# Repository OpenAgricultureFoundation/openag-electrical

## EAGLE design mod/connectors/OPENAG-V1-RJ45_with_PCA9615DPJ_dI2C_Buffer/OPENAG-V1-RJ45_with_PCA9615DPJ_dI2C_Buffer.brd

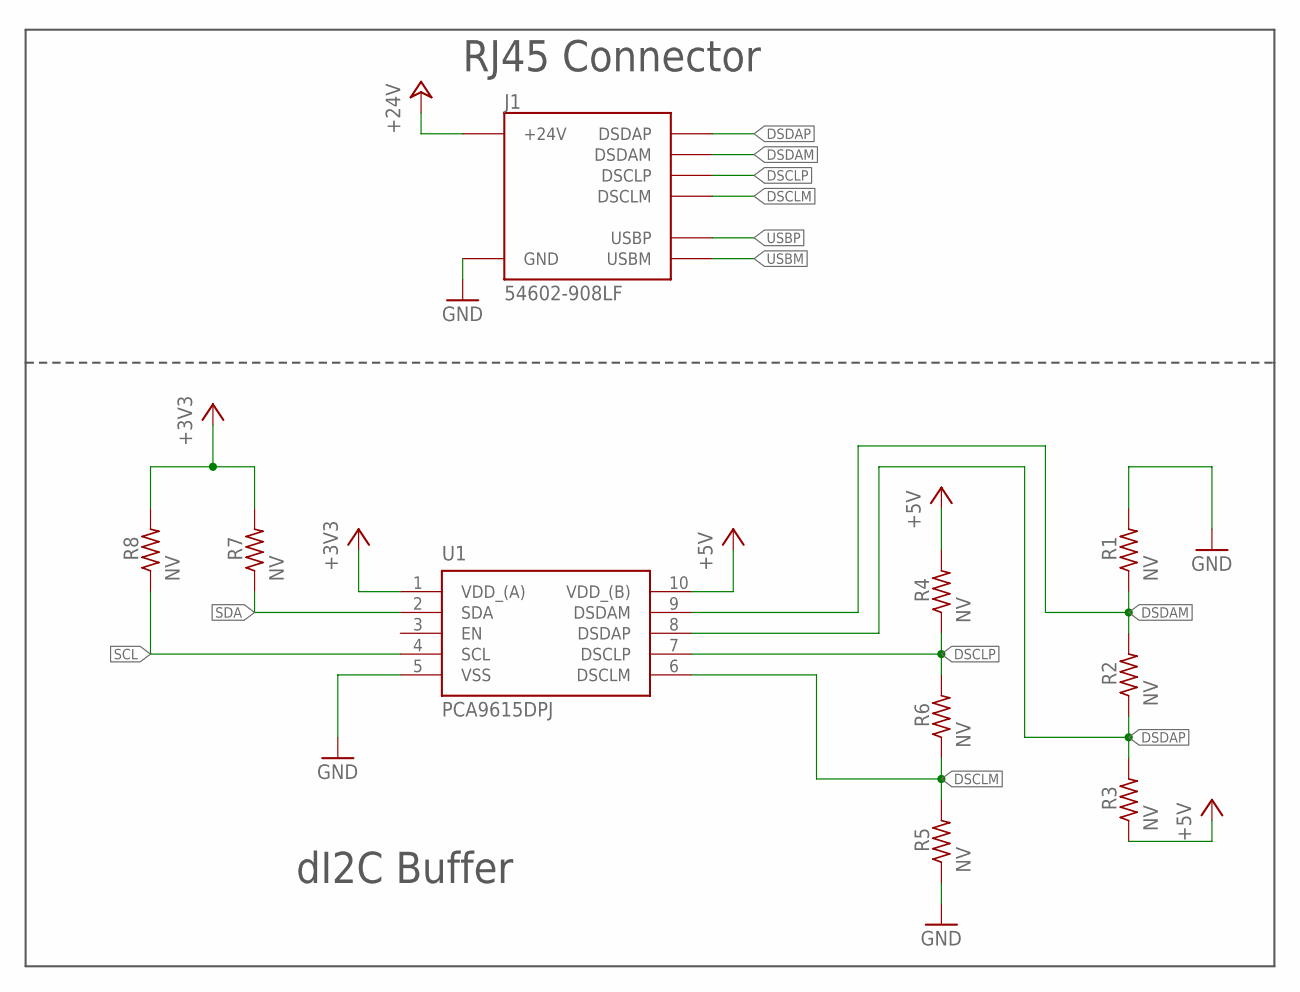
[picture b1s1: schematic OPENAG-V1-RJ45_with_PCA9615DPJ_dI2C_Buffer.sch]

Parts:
J1: 54602-908LF; OPENAG-V1-RJ45
R1, R2, R3, R4, R5, R6, R7, R8: NV; RC0603N
U1: PCA9615DPJ; SOP50P490X110-10N

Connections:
+3V3: R7.2, R8.2, U1.1 (VDD_(A))
+5V: R3.1, R4.2, U1.10 (VDD_(B))
+24V: J1.24V(6) (+24V)
DSCLM: J1.DSCLM(5) (DSCLM), R5.2, R6.1, U1.6 (DSCLM)
DSCLP: J1.DSCLP(4) (DSCLP), R4.1, R6.2, U1.7 (DSCLP)
DSDAM: J1.DSDAM(2) (DSDAM), R1.1, R2.2, U1.9 (DSDAM)
DSDAP: J1.DSDAP(1) (DSDAP), R2.1, R3.2, U1.8 (DSDAP)
GND: J1.GND(3) (GND), R1.2, R5.1, U1.5 (VSS)
SCL: R8.1, U1.4 (SCL)
SDA: R7.1, U1.2 (SDA)
USBM: J1.USBM(8) (USBM)
USBP: J1.USBP(7) (USBP)

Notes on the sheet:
dI2C Buffer
RJ45 Connector

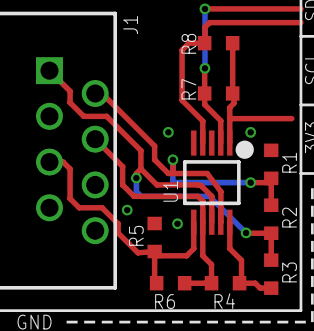
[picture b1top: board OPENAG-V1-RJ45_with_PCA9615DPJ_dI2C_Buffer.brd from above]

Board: 2 copper layers, 10 parts (0 on the bottom side), 9 nets.

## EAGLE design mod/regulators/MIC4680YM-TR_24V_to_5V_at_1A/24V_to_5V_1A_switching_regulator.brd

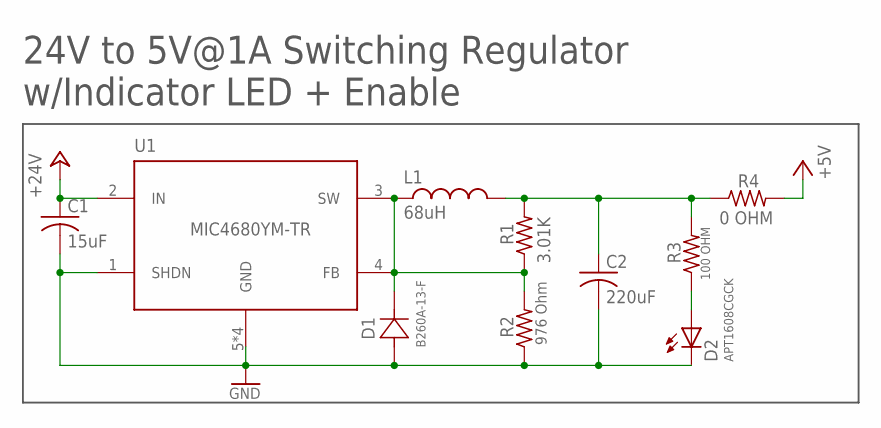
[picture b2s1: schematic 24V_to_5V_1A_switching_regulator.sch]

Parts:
C1: 15uF; CT7343
C2: 220uF; CT7343
D1: B260A-13-F; SMA
D2: APT1608CGCK; CHIPLED_0603
L1: 68uH; UP2B
R1: 3.01K; RC0603N
R2: 976 Ohm; RC0603N
R3: 100 OHM; RC0603N
R4: 0 OHM; RC0603N
U1: MIC4680YM-TR; SOIC8

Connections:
+5V: R4.2
+24V: C1.+ (1(+)), U1.2 (IN)
GND: C1.- (2(-)), C2.- (2(-)), D1.2 (21), D2.C, R2.1, U1.1 (SHDN), U1.5 (GND), U1.6 (GND), U1.7 (GND), U1.8 (GND)
unnamed: D2.A, R3.1
unnamed: C2.+ (1(+)), L1.2, R1.2, R3.2, R4.1
unnamed: D1.1 (12), L1.1, R1.1, R2.2, U1.3 (SW), U1.4 (FB)

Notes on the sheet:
24V to 5V@1A Switching Regulator w/Indicator LED + Enable

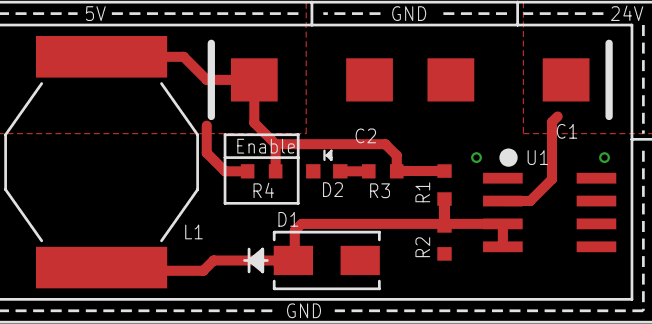
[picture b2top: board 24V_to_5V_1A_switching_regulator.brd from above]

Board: 2 copper layers, 10 parts (0 on the bottom side), 5 nets.

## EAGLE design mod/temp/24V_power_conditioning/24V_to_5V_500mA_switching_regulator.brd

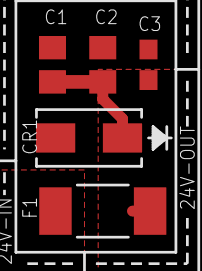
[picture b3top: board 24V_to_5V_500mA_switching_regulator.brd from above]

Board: 2 copper layers, 6 parts (0 on the bottom side), 2 nets.

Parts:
C1: 10uF; C0805
C2: 4.7uF; C0805
C3: 0.1uF; C0603
CR1: SMAJ26A-13-F; SMA
F1: SST 7; SS
U$2: OPENAG-LOGO-750-MIL

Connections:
+24V: C1.1, C2.1, C3.1, CR1.1, F1.2
GND: C1.2, C2.2, C3.2, CR1.2

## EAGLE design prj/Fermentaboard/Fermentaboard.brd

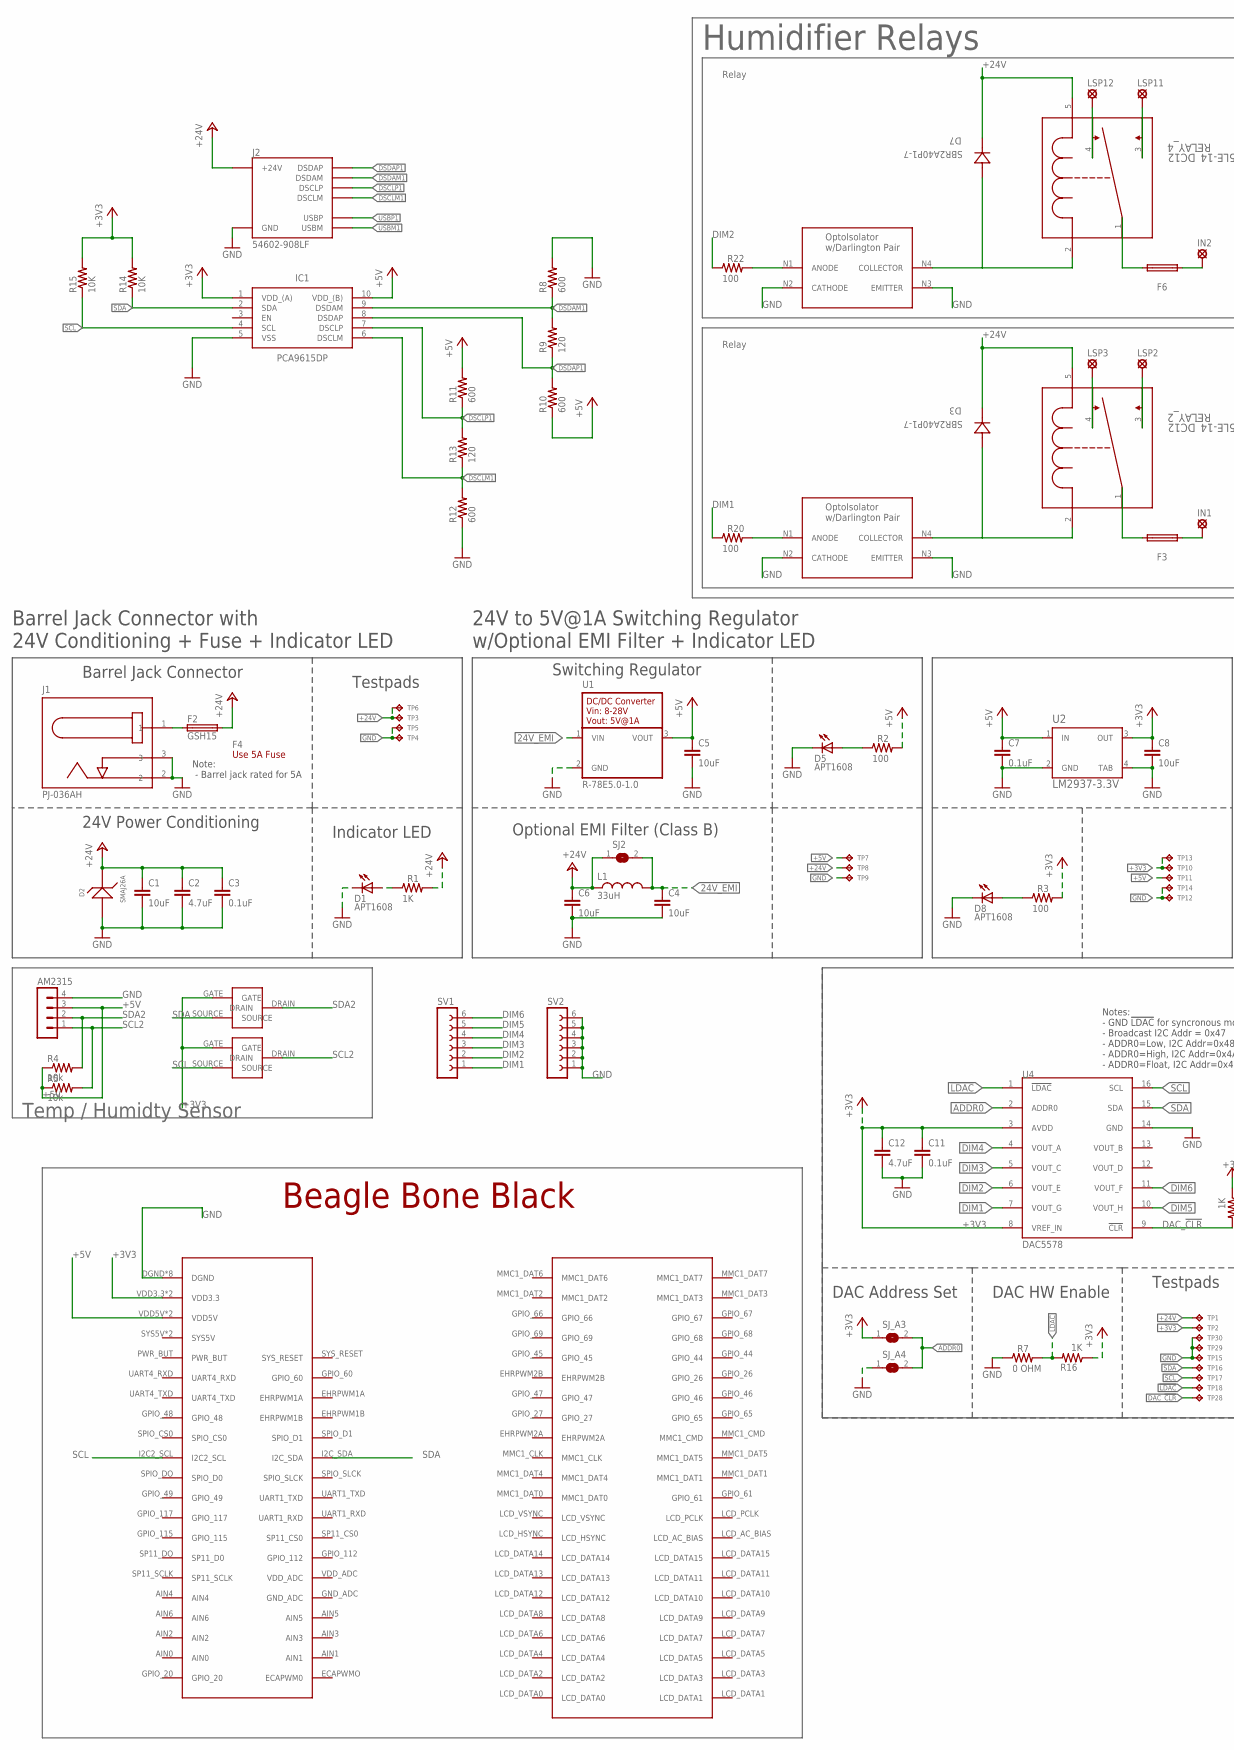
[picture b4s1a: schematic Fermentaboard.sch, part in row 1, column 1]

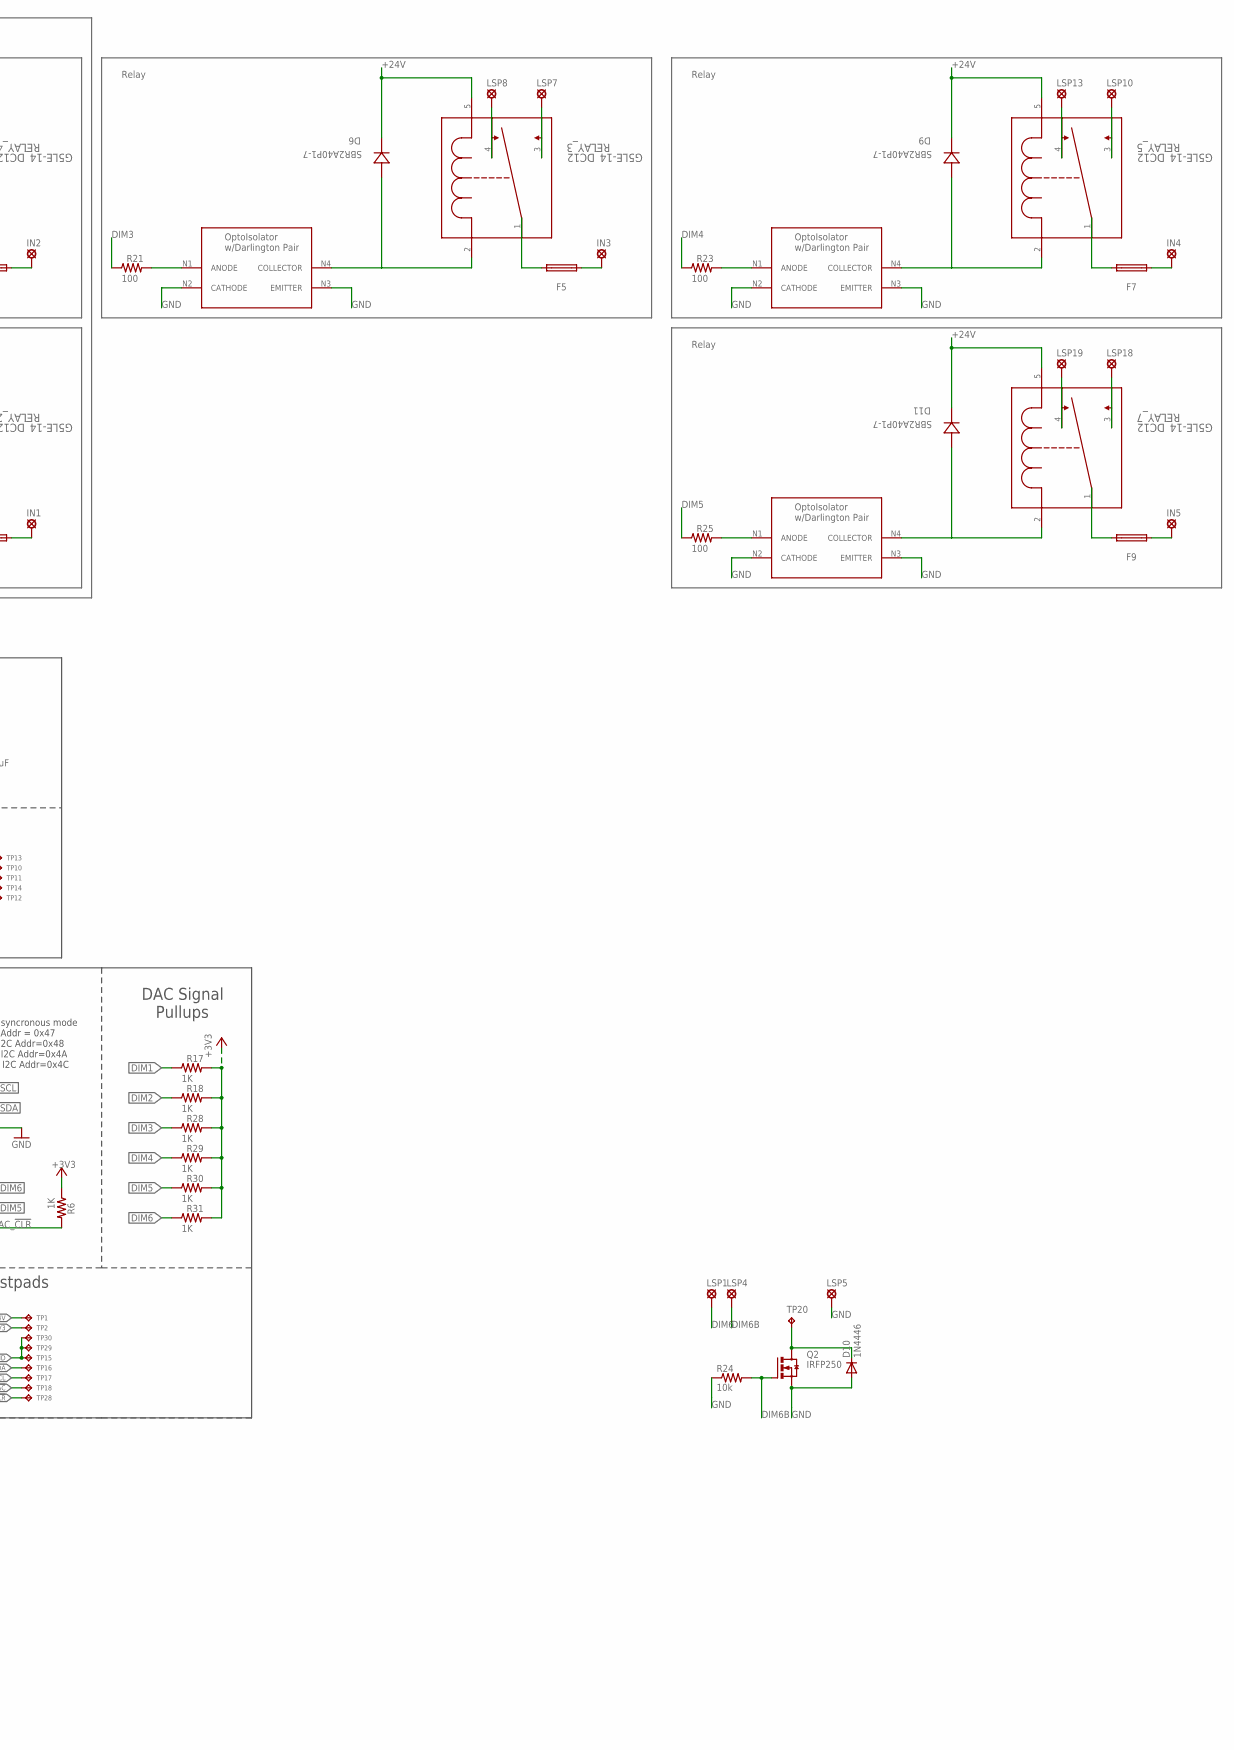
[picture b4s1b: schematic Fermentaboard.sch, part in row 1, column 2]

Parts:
AM2315: MA04-1
C1, C4, C5, C6, C8: 10uF; C0805
C2, C12: 4.7uF; C0805
C3, C7, C11: 0.1uF; C0603
D1, D5, D8: APT1608; CHIPLED_0603
D2: SMAJ26A; SMA
D3, D6, D7, D9, D11: SBR2A40P1-7; POWERDI123
D10: 1N4446; DO35-10
F2, F3, F5, F6, F7, F9: GSH15
F4: Use 5A Fuse; FUSE-CARTRIDGE
IC1: PCA9615DP; SOP50P490X110-10N
IN1, IN2, IN3, IN4, IN5: SE14
J1: PJ-036AH; BARREL-JACK-PJ-036AH
J2: 54602-908LF; OPENAG-V1-RJ45
L1: 33uH; 29333C
LSP1, LSP4, LSP5: LSP11
LSP2, LSP3, LSP7, LSP8, LSP10, LSP11, LSP12, LSP13, LSP18, LSP19: SE14
Q2: IRFP250; TO-247AD-V
R1, R6, R16, R17, R18, R28, R29, R30, R31: 1K; RC0603N
R2, R3, R20, R21, R22, R23, R25: 100; RC0603N
R4, R5, R24: 10k; R0603
R7: 0 OHM; RC0603N
R8, R10, R11, R12: 600; R0603
R9, R13: 120; R0603
R14, R15: 10K; R0603
RELAY_2, RELAY_3, RELAY_4, RELAY_5, RELAY_7: G5LE-14_DC12; RELAY_G5LE-1
SJ2: EMI-BYPASS
SJ_A3, SJ_A4: SOLDERJUMPERREFLOW_NOPASTE; SJ1
SV1, SV2: FE06-1; FE06
TP1, TP2, TP3, TP4, TP5, TP6, TP10, TP11, TP12, TP13, TP14, TP15, TP16, TP17, TP18, TP28, TP29, TP30: TPTP04R; TP04R
TP7, TP8, TP9: TPTP06R; TP06R
TP20: TPPAD1-13; P1-13
U1: R-78E5.0-1.0
U2: LM2937-3.3V; MP04A
U4: DAC5578; TSSOP16
U$2: BBB_SMD; 23PINHEADERSMD
U$3, U$4: BSS138; SOT23
U$6, U$7, U$8, U$9, U$11: LTV-355T

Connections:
24V_EMI: C4.1, L1.2, SJ2.2, U1.1 (VIN)
24V_IN1: F2.1, J1.1
!LDAC!: R7.2, R16.2, TP18.1, U4.1 (!LDAC!)
+3V3: C8.1, C11.1, C12.1, IC1.1 (VDD_(A)), R3.2, R6.1, R14.2, R15.2, R16.1, R17.2, R18.2, R28.2, R29.2, R30.2, R31.2, SJ_A3.1, TP2.1, TP10.1, TP13.1, U2.3 (OUT), U4.3 (AVDD), U4.8 (VREF_IN), U$2.VDD3.3, U$2.VDD3.31 (VDD3.3), U$3.GATE, U$4.GATE
+5V: AM2315.3, C5.1, C7.1, IC1.10 (VDD_(B)), R2.2, R4.1, R5.1, R10.1, R11.2, TP7.TP, TP11.1, U1.3 (VOUT), U2.1 (IN), U$2.VDD5V, U$2.VDD5V1 (VDD5V)
+24V: C1.1, C2.1, C3.1, C6.1, D2.1, D3.-, D6.-, D7.-, D9.-, D11.-, F2.2, J2.24V(6) (+24V), L1.1, R1.2, RELAY_2.5, RELAY_3.5, RELAY_4.5, RELAY_5.5, RELAY_7.5, SJ2.1, TP1.1, TP3.1, TP6.1, TP8.TP
ADDR0: SJ_A3.2, SJ_A4.2, U4.2 (ADDR0)
DAC_!CLR!: R6.2, TP28.1, U4.9 (!CLR!)
DIM1: R17.1, R20.1, SV1.1, U4.7 (VOUT_G)
DIM2: R18.1, R22.1, SV1.2, U4.6 (VOUT_E)
DIM3: R21.1, R28.1, SV1.3, U4.5 (VOUT_C)
DIM4: R23.1, R29.1, SV1.4, U4.4 (VOUT_A)
DIM5: R25.1, R30.1, SV1.5, U4.10 (VOUT_H)
DIM6: LSP1.MP, R31.1, SV1.6, U4.11 (VOUT_F)
DIM6B: LSP4.MP, Q2.G, R24.2
DSCLM1: IC1.6 (DSCLM), J2.DSCLM(5) (DSCLM), R12.2, R13.1
DSCLP1: IC1.7 (DSCLP), J2.DSCLP(4) (DSCLP), R11.1, R13.2
DSDAM1: IC1.9 (DSDAM), J2.DSDAM(2) (DSDAM), R8.1, R9.2
DSDAP1: IC1.8 (DSDAP), J2.DSDAP(1) (DSDAP), R9.1, R10.2
GND: AM2315.4, C1.2, C2.2, C3.2, C4.2, C5.2, C6.2, C7.2, C8.2, C11.2, C12.2, D1.C, D2.2, D5.C, D8.C, D10.A, IC1.5 (VSS), J1.2, J1.3, J2.GND(3) (GND), LSP5.MP, Q2.S, R7.1, R8.2, R12.1, R24.1, SJ_A4.1, SV2.1, SV2.2, SV2.3, SV2.4, SV2.5, SV2.6, TP4.1, TP5.1, TP9.TP, TP12.1, TP14.1, TP15.1, TP29.1, TP30.1, U1.2 (GND), U2.2 (GND), U2.4 (TAB), U4.14 (GND), U$2.DGND, U$2.DGND1 (DGND), U$2.DGND2 (DGND), U$2.DGND3 (DGND), U$2.DGND4 (DGND), U$2.DGND5 (DGND), U$2.DGND6 (DGND), U$2.DGND7 (DGND), U$6.N2 (CATHODE), U$6.N3 (EMITTER), U$7.N2 (CATHODE), U$7.N3 (EMITTER), U$8.N2 (CATHODE), U$8.N3 (EMITTER), U$9.N2 (CATHODE), U$9.N3 (EMITTER), U$11.N2 (CATHODE), U$11.N3 (EMITTER)
unnamed: D1.A, R1.1
unnamed: D3.+, RELAY_2.2 (1), U$6.N4 (COLLECTOR)
unnamed: D5.A, R2.1
unnamed: F3.2, RELAY_2.1 (2)
unnamed: LSP2.MP, RELAY_2.3
unnamed: D8.A, R3.1
unnamed: R20.2, U$6.N1 (ANODE)
unnamed: LSP3.MP, RELAY_2.4
unnamed: F3.1, IN1.MP
unnamed: D10.C, Q2.D, TP20.TP
unnamed: D6.+, RELAY_3.2 (1), U$7.N4 (COLLECTOR)
unnamed: F5.2, RELAY_3.1 (2)
unnamed: LSP7.MP, RELAY_3.3
unnamed: R21.2, U$7.N1 (ANODE)
unnamed: LSP8.MP, RELAY_3.4
unnamed: F5.1, IN3.MP
unnamed: D7.+, RELAY_4.2 (1), U$8.N4 (COLLECTOR)
unnamed: F6.2, RELAY_4.1 (2)
unnamed: LSP11.MP, RELAY_4.3
unnamed: R22.2, U$8.N1 (ANODE)
unnamed: LSP12.MP, RELAY_4.4
unnamed: F6.1, IN2.MP
unnamed: D9.+, RELAY_5.2 (1), U$9.N4 (COLLECTOR)
unnamed: F7.2, RELAY_5.1 (2)
unnamed: LSP10.MP, RELAY_5.3
unnamed: R23.2, U$9.N1 (ANODE)
unnamed: LSP13.MP, RELAY_5.4
unnamed: F7.1, IN4.MP
unnamed: D11.+, RELAY_7.2 (1), U$11.N4 (COLLECTOR)
unnamed: F9.2, RELAY_7.1 (2)
unnamed: LSP18.MP, RELAY_7.3
unnamed: R25.2, U$11.N1 (ANODE)
unnamed: LSP19.MP, RELAY_7.4
unnamed: F9.1, IN5.MP
SCL: IC1.4 (SCL), R15.1, TP17.1, U4.16 (SCL), U$2.I2C2_SCL, U$4.SOURCE
SCL2: AM2315.1, R5.2, U$4.DRAIN
SDA: IC1.2 (SDA), R14.1, TP16.1, U4.15 (SDA), U$2.I2C_SDA, U$3.SOURCE
SDA2: AM2315.2, R4.2, U$3.DRAIN
USBM1: J2.USBM(8) (USBM)
USBP1: J2.USBP(7) (USBP)

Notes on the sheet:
Barrel Jack Connector
Barrel Jack Connector with 24V Conditioning + Fuse + Indicator LED
24V Power Conditioning
Indicator LED
Testpads
Note: - Barrel jack rated for 5A
24V to 5V@1A Switching Regulator w/Optional EMI Filter + Indicator LED
Switching Regulator
Optional EMI Filter (Class B)
Notes: - GND !LDAC! for syncronous mode - Broadcast I2C Addr = 0x47 - ADDR0=Low, I2C Addr=0x48 - ADDR0=High, I2C Addr=0x4A - ADDR0=Float, I2C Addr=0x4C
DAC Signal Pullups
DAC Address Set
DAC HW Enable
Relay
Humidifier Relays
Temp / Humidty Sensor

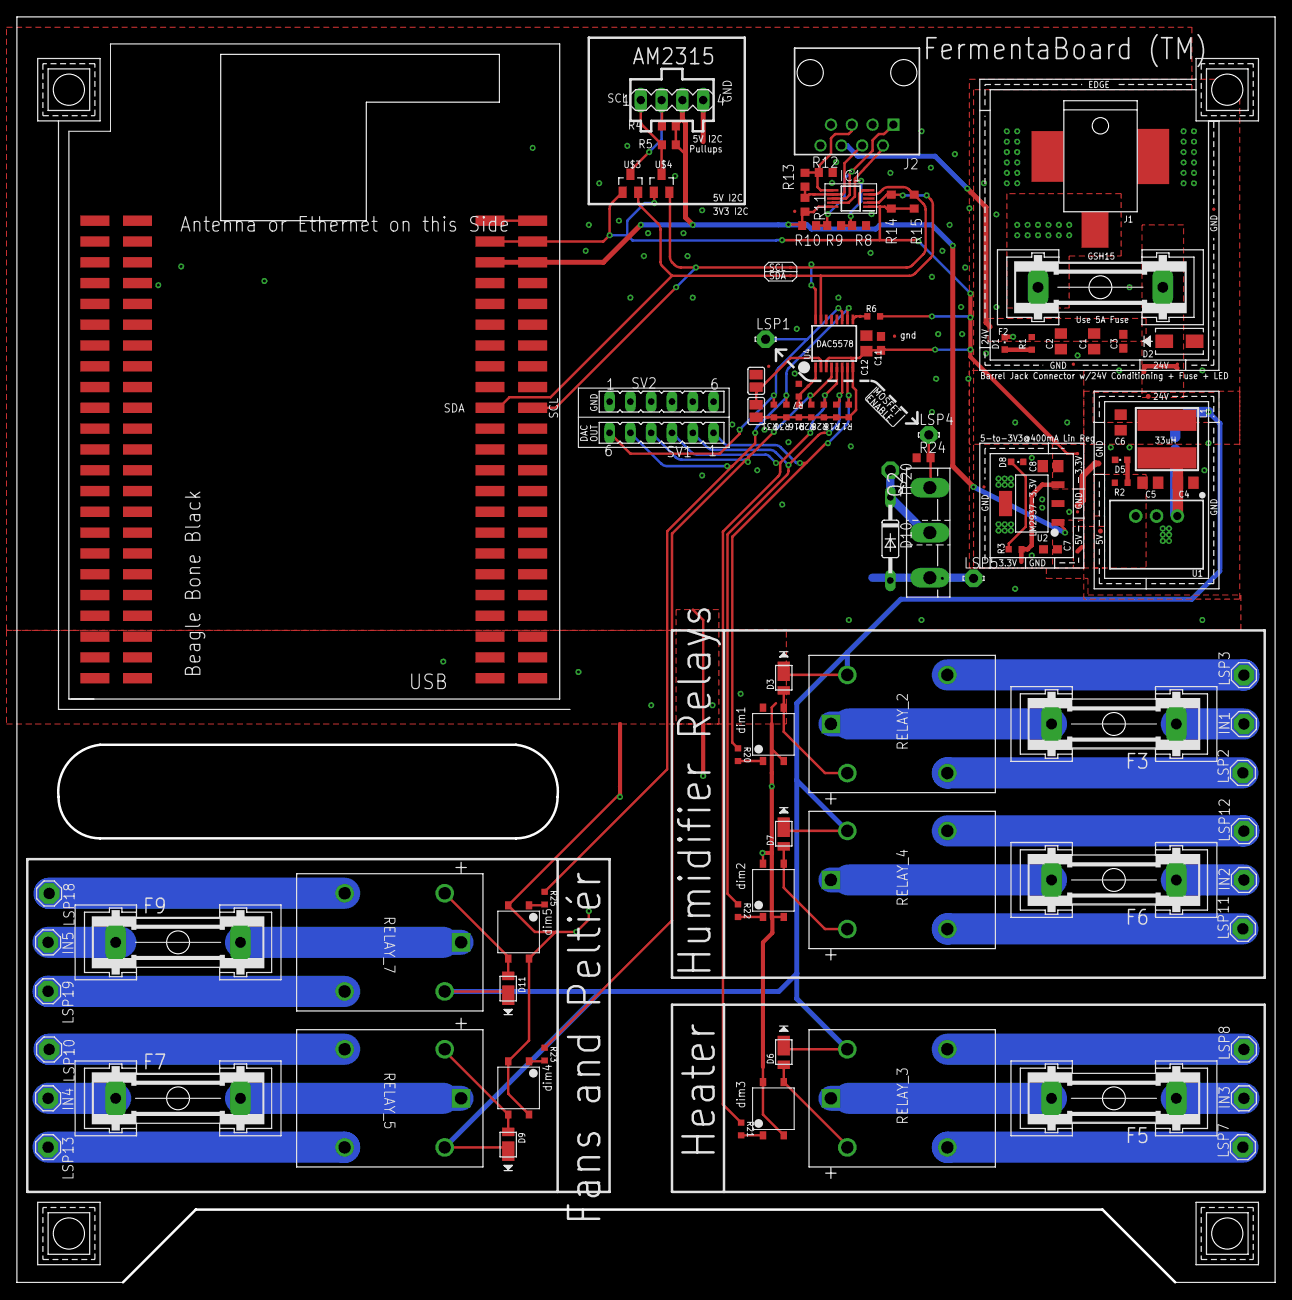
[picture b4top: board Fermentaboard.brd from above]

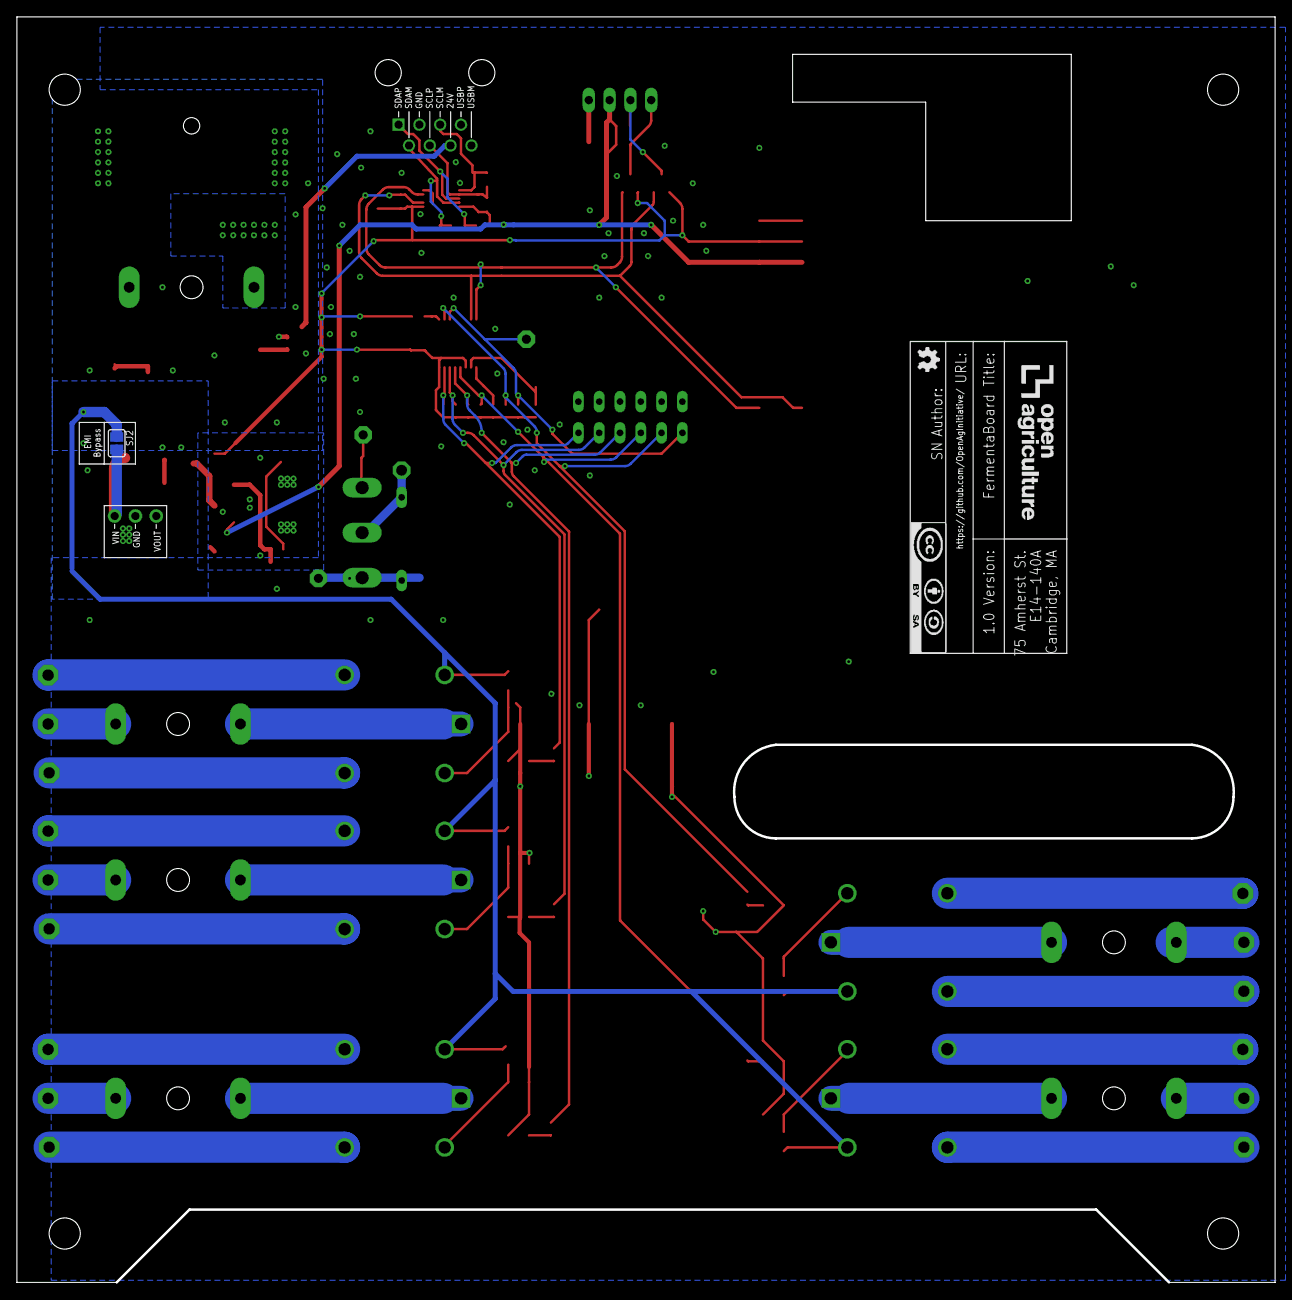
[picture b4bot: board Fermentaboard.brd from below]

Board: 2 copper layers, 153.7 x 154.6 mm, 127 parts (2 on the bottom side), 58 nets.

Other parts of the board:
ATTRIBUTES: DOCFIELD
U$1, U$5, U$10, U$12: CORNER

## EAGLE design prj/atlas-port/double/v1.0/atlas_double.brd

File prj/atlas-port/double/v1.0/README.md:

# Atlas Port Double v1.0
Port for connection x2 Atlas Probes. Includes isolation circuitry
and recepticle for atlas stamp. Has headers and mounting point for
connection with larger board.

### Contents
1. [Schematic](#schematic)
2. [Board](#board)
2. [Board Top](#board-top)
3. [Board Bottom](#board-bottom)
4. [Bill of Materials](atlas_double.csv)
5. [Gerber Files](atlas_port_double_v_1_0.zip)

### Schematic

### Board

### Board Top

### Board Bottom

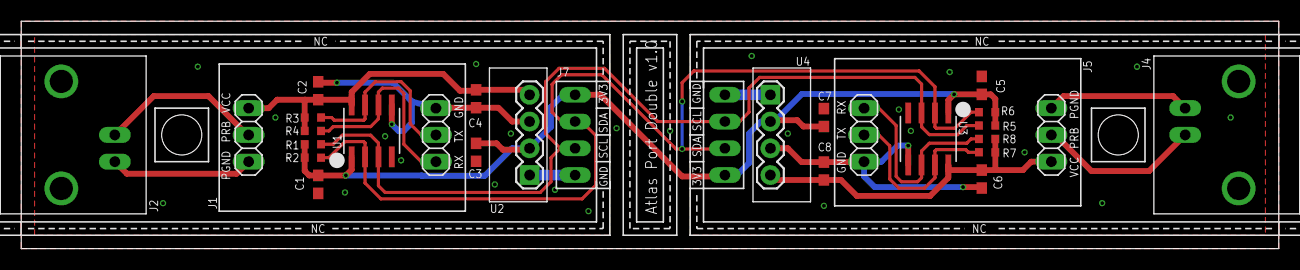
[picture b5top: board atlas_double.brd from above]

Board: 2 copper layers, 119.4 x 21.6 mm, 28 parts (0 on the bottom side), 16 nets.

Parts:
C1, C2, C3, C4, C5, C6, C7, C8: 0.1uF; C0603
J1, J5: Atlas Stamp; ATLAS-STAMP
J2, J4: 5227161-9; BNC-5227161
J7: ATLAS-DOUBLE-CONN; ATLAS-DOUBLE
R1, R2, R3, R4, R5, R6, R7, R8: 1K; RC0603N
U1, U3: ISO1540; D8
U2, U4: RM-3.33.3S; RM3.33.3S-SIP4
U$1, U$2: HOLE-150
U$3: CAMBRIDGE-MAP-X1-ATLAS-DOUBLE-V-1-0

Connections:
+3V3: C1.1, C3.1, C5.1, C7.1, J7.3V3@1, J7.3V3@2, R1.2, R2.2, R5.2, R6.2, U1.1, U2.2, U3.1, U4.2
GND: C1.2, C3.2, C5.2, C7.2, J7.GND@1, J7.GND@2, U1.4, U2.1, U3.4, U4.1
ISO_3V3_1: C2.1, C4.1, J1.4, R3.2, R4.2, U1.8, U2.4
ISO_3V3_2: C6.1, C8.1, J5.4, R7.2, R8.2, U3.8, U4.4
ISO_GND_1: C2.2, C4.2, J1.3, U1.5, U2.3
ISO_GND_2: C6.2, C8.2, J5.3, U3.5, U4.3
ISO_SCL_1: J1.1, R4.1, U1.6
ISO_SCL_2: J5.1, R8.1, U3.6
ISO_SDA_1: J1.2, R3.1, U1.7
ISO_SDA_2: J5.2, R7.1, U3.7
PGND_1: J1.6, J2.GND
PGND_2: J4.GND, J5.6
PRB_1: J1.5, J2.S
PRB_2: J4.S, J5.5
SCL: J7.SCL@1, J7.SCL@2, R1.1, R5.1, U1.3, U3.3
SDA: J7.SDA@1, J7.SDA@2, R2.1, R6.1, U1.2, U3.2

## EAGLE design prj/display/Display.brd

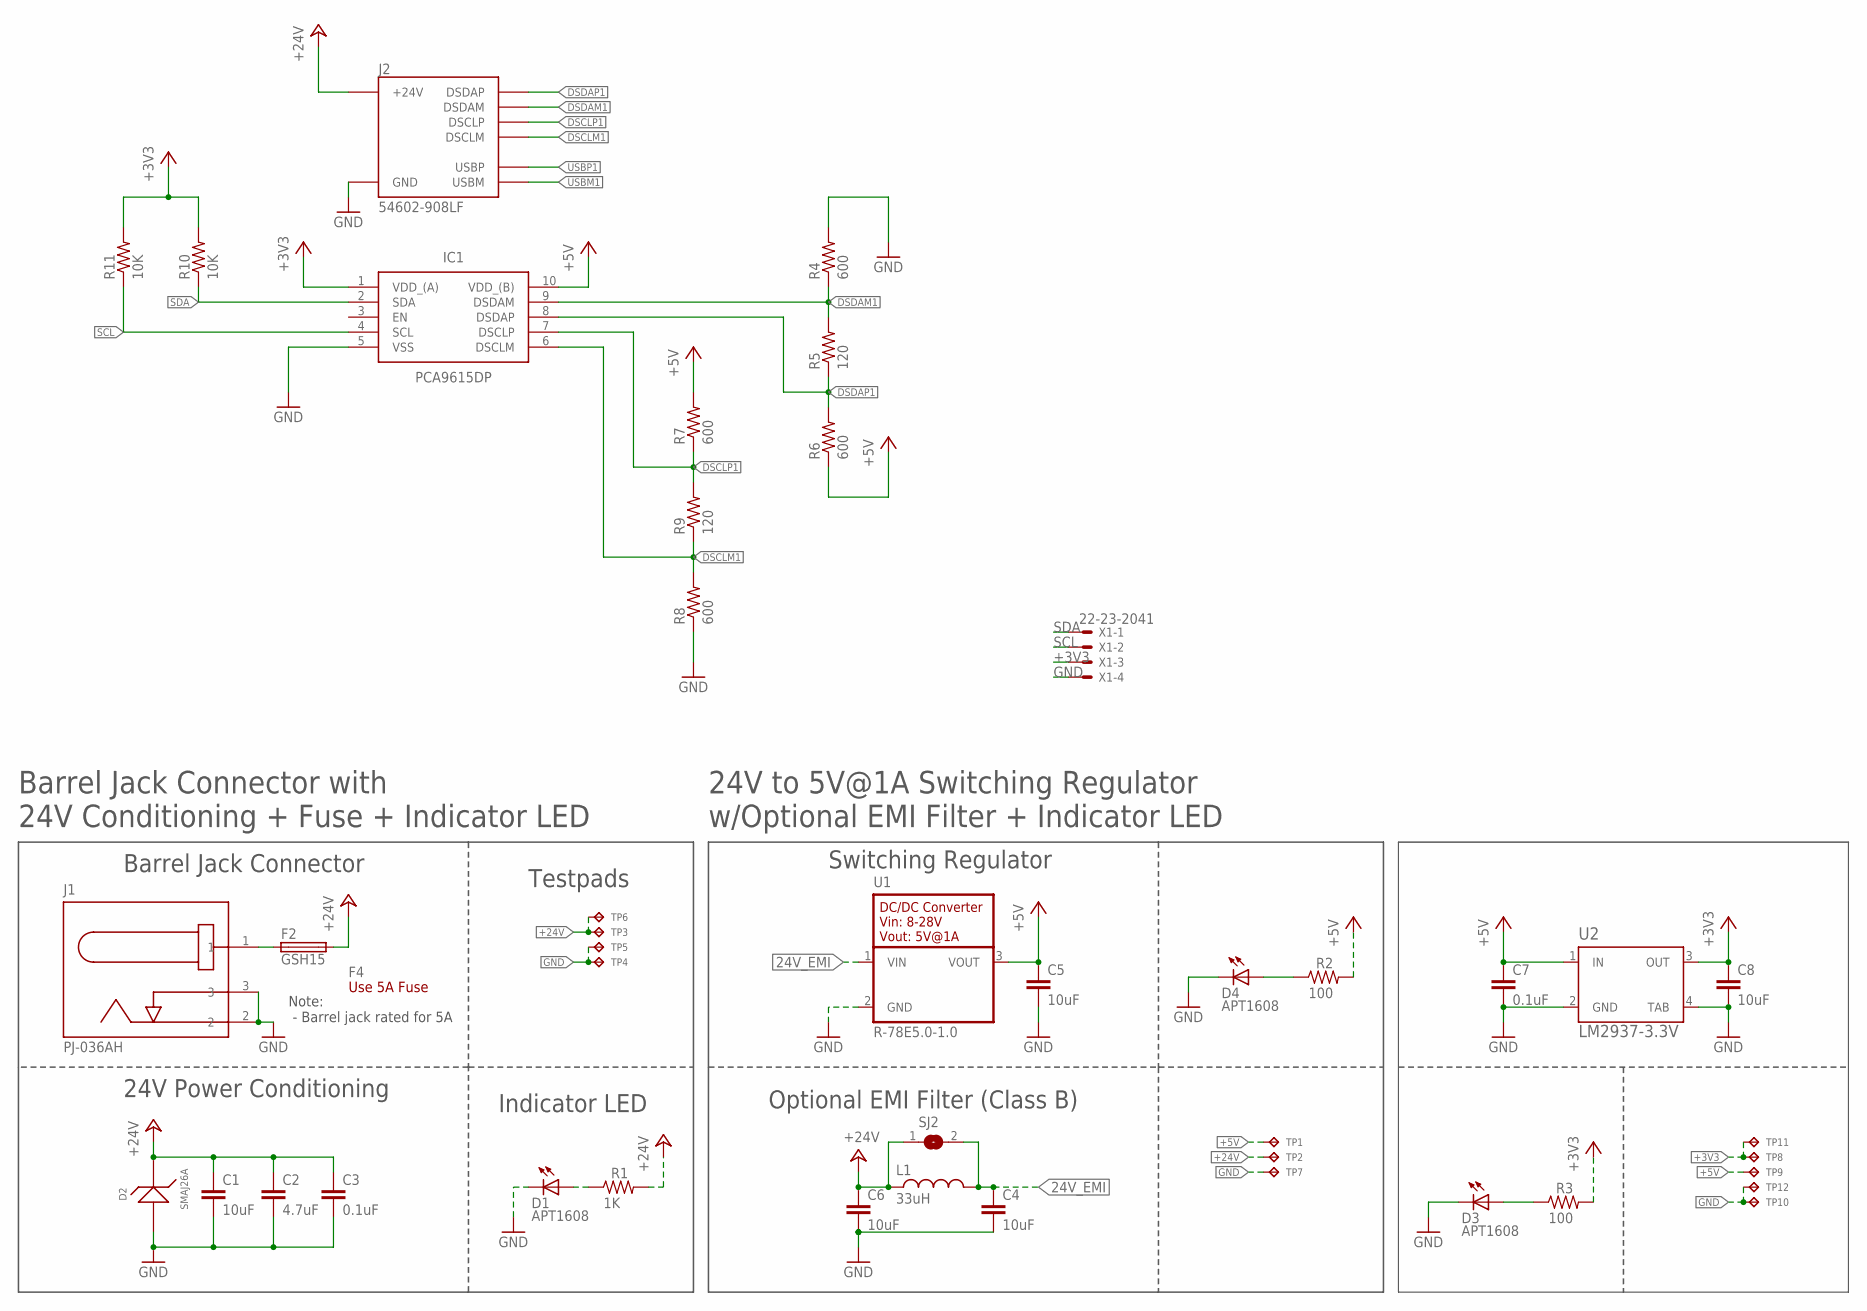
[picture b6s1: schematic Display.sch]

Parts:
C1, C4, C5, C6, C8: 10uF; C0805
C2: 4.7uF; C0805
C3, C7: 0.1uF; C0603
D1, D3, D4: APT1608; CHIPLED_0603
D2: SMAJ26A; SMA
F2: GSH15
F4: Use 5A Fuse; FUSE-CARTRIDGE
IC1: PCA9615DP; SOP50P490X110-10N
J1: PJ-036AH; BARREL-JACK-PJ-036AH
J2: 54602-908LF; OPENAG-V1-RJ45
L1: 33uH; 29333C
R1: 1K; RC0603N
R2, R3: 100; RC0603N
R4, R6, R7, R8: 600; R0603
R5, R9: 120; R0603
R10, R11: 10K; R0603
SJ2: EMI-BYPASS
TP1, TP2, TP7: TPTP06R; TP06R
TP3, TP4, TP5, TP6, TP8, TP9, TP10, TP11, TP12: TPTP04R; TP04R
U1: R-78E5.0-1.0
U2: LM2937-3.3V; MP04A
X1: 22-23-2041

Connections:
24V_EMI: C4.1, L1.2, SJ2.2, U1.1 (VIN)
24V_IN1: F2.1, J1.1
+3V3: C8.1, IC1.1 (VDD_(A)), R3.2, R10.2, R11.2, TP8.1, TP11.1, U2.3 (OUT), X1.3
+5V: C5.1, C7.1, IC1.10 (VDD_(B)), R2.2, R6.1, R7.2, TP1.TP, TP9.1, U1.3 (VOUT), U2.1 (IN)
+24V: C1.1, C2.1, C3.1, C6.1, D2.1, F2.2, J2.24V(6) (+24V), L1.1, R1.2, SJ2.1, TP2.TP, TP3.1, TP6.1
DSCLM1: IC1.6 (DSCLM), J2.DSCLM(5) (DSCLM), R8.2, R9.1
DSCLP1: IC1.7 (DSCLP), J2.DSCLP(4) (DSCLP), R7.1, R9.2
DSDAM1: IC1.9 (DSDAM), J2.DSDAM(2) (DSDAM), R4.1, R5.2
DSDAP1: IC1.8 (DSDAP), J2.DSDAP(1) (DSDAP), R5.1, R6.2
GND: C1.2, C2.2, C3.2, C4.2, C5.2, C6.2, C7.2, C8.2, D1.C, D2.2, D3.C, D4.C, IC1.5 (VSS), J1.2, J1.3, J2.GND(3) (GND), R4.2, R8.1, TP4.1, TP5.1, TP7.TP, TP10.1, TP12.1, U1.2 (GND), U2.2 (GND), U2.4 (TAB), X1.4
unnamed: D1.A, R1.1
unnamed: D4.A, R2.1
unnamed: D3.A, R3.1
SCL: IC1.4 (SCL), R11.1, X1.2
SDA: IC1.2 (SDA), R10.1, X1.1
USBM1: J2.USBM(8) (USBM)
USBP1: J2.USBP(7) (USBP)

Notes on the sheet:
Barrel Jack Connector
Barrel Jack Connector with 24V Conditioning + Fuse + Indicator LED
24V Power Conditioning
Indicator LED
Testpads
Note: - Barrel jack rated for 5A
24V to 5V@1A Switching Regulator w/Optional EMI Filter + Indicator LED
Switching Regulator
Optional EMI Filter (Class B)

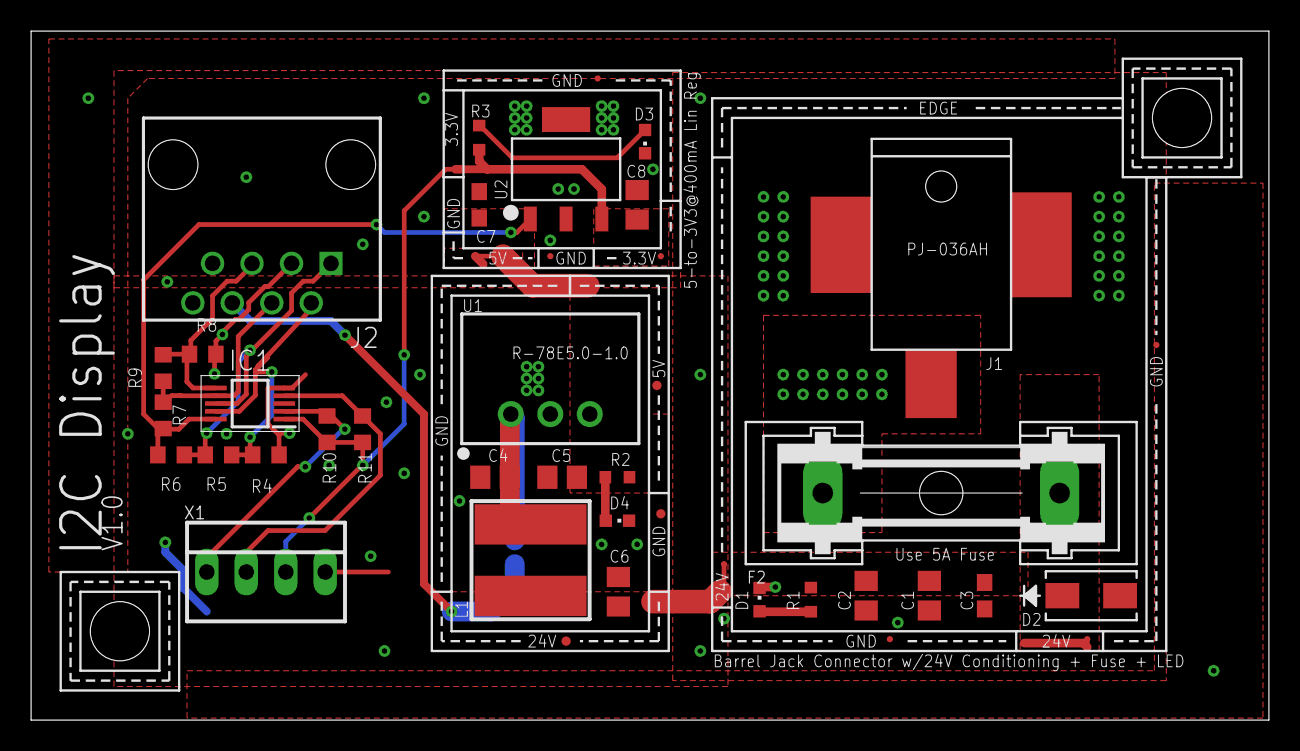
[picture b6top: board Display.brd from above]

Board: 2 copper layers, 79.6 x 44.3 mm, 47 parts (1 on the bottom side), 15 nets.

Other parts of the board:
U$1, U$2: CORNER
